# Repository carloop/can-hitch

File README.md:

# CAN Hitch
## _A CAN Bus Transceiver Breakout_

Connect microcontrollers together with CAN bus.

- [Schematics](CAN-breakout-3.3V-v3.pdf)
- [Bill of materials](CAN-breakout-3.3V-v3_BOM.csv)

## License

Copyright 2017 Carloop
Released under the MIT license

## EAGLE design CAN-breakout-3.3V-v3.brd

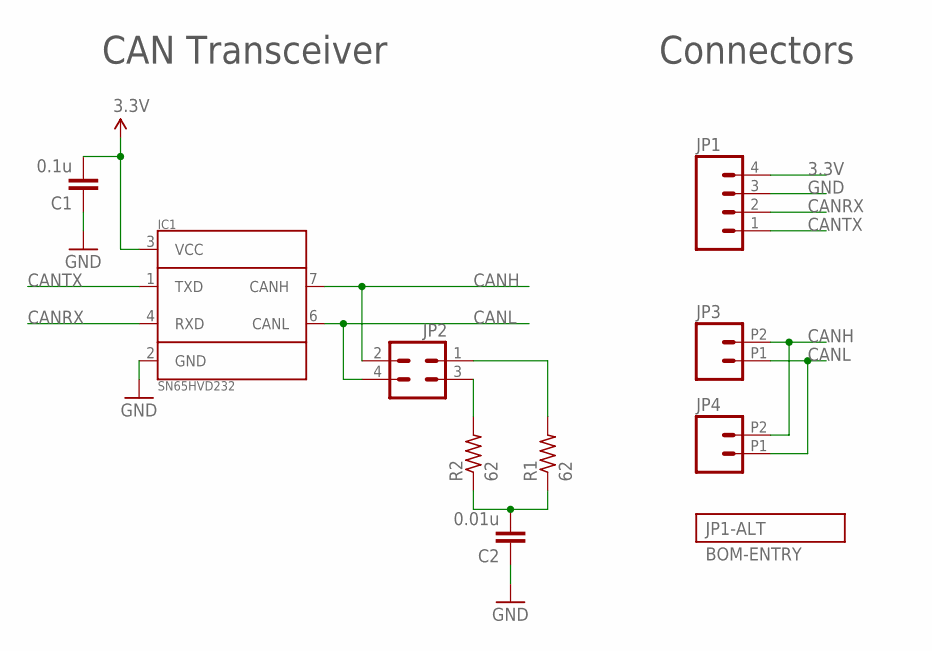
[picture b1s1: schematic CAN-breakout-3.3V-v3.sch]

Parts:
C1: 0.1u; C1206; PARTNO 12065C104KAT2A
C2: 0.01u; C1206; PARTNO 12065C103KAT2A
IC1: SN65HVD232; SO8; PARTNO SN65HVD232DR
JP1: M04PTH; 1X04; PARTNO PREC004SAAN-RC
JP2: M02X2; 2X2; PARTNO PREC002DAAN-RC
JP3, JP4: M022.54MM_SCREWTERM; 1X02_2.54_SCREWTERM; PARTNO OSTVN02A150
R1, R2: 62; R1206; PARTNO RC1206FR-0762RL

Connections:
3.3V: C1.2, IC1.3 (VCC), JP1.4
CANH: IC1.7 (CANH), JP2.2, JP3.P2 (2), JP4.P2 (2)
CANL: IC1.6 (CANL), JP2.4, JP3.P1 (1), JP4.P1 (1)
CANRX: IC1.4 (RXD), JP1.2
CANTX: IC1.1 (TXD), JP1.1
GND: C1.1, C2.1, IC1.2 (GND), JP1.3
unnamed: JP2.1, R1.2
unnamed: C2.2, R1.1, R2.1
unnamed: JP2.3, R2.2

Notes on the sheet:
CAN Transceiver
Connectors

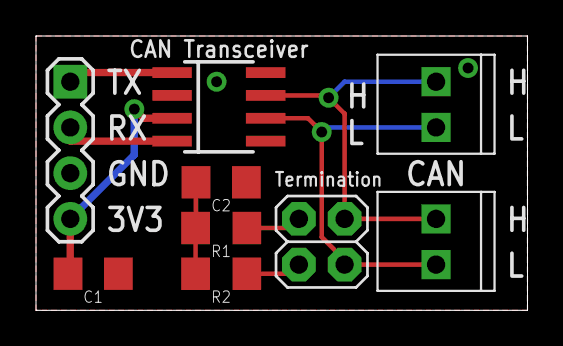
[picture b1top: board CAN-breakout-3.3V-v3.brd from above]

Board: 2 copper layers, 27.3 x 15.2 mm, 9 parts (0 on the bottom side), 9 nets.

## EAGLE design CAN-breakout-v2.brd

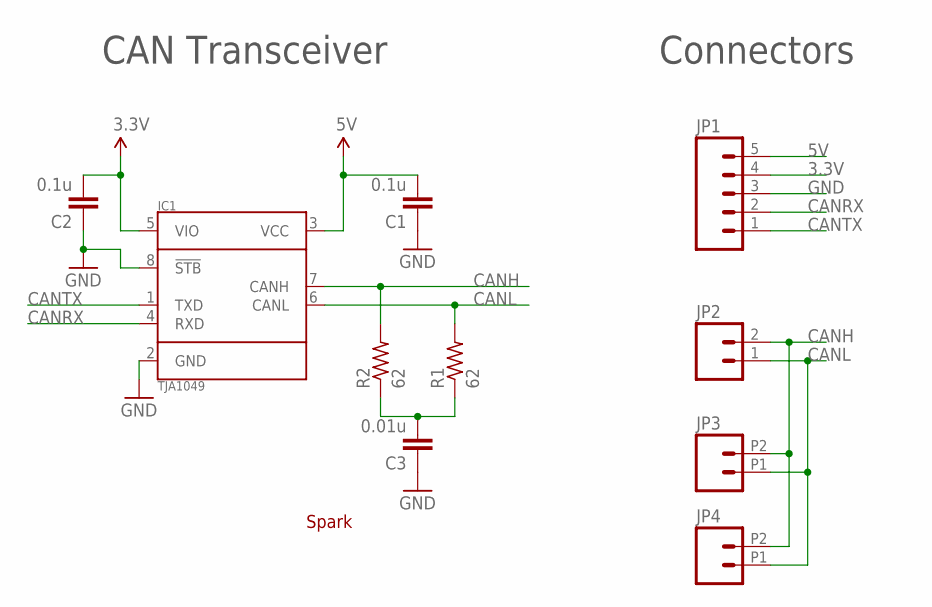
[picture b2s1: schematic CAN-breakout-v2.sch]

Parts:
C1, C2: 0.1u; C1206; PARTNO 12065C104KAT2A
C3: 0.01u; C1206; PARTNO 12065C103KAT2A
IC1: TJA1049; SO8; PARTNO TJA1049T-118
JP1: M05PTH; 1X05; PARTNO PREC005SAAN-RC
JP2: M02PTH; 1X02; PARTNO PREC002SAAN-RC
JP3, JP4: M022.54MM_SCREWTERM; 1X02_2.54_SCREWTERM; PARTNO OSTVN02A150
R1, R2: 62; R1206; PARTNO RC1206FR-0762RL
U$3: SPARK_LOGO2

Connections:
3.3V: C2.2, IC1.5 (VIO), JP1.4
5V: C1.2, IC1.3 (VCC), JP1.5
CANH: IC1.7 (CANH), JP2.2, JP3.P2 (2), JP4.P2 (2), R2.2
CANL: IC1.6 (CANL), JP2.1, JP3.P1 (1), JP4.P1 (1), R1.2
CANRX: IC1.4 (RXD), JP1.2
CANTX: IC1.1 (TXD), JP1.1
GND: C1.1, C2.1, C3.1, IC1.2 (GND), IC1.8 (!STB), JP1.3
unnamed: C3.2, R1.1, R2.1

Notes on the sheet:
CAN Transceiver
Connectors

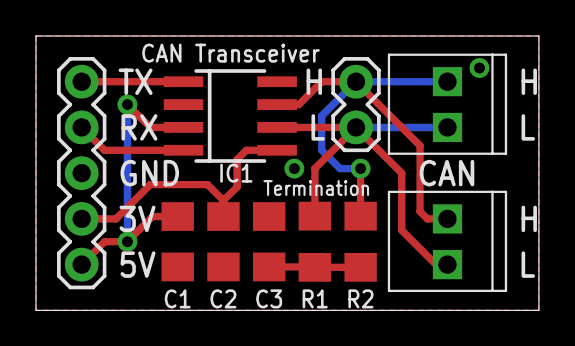
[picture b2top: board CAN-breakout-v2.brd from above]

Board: 2 copper layers, 27.9 x 15.2 mm, 11 parts (1 on the bottom side), 8 nets.

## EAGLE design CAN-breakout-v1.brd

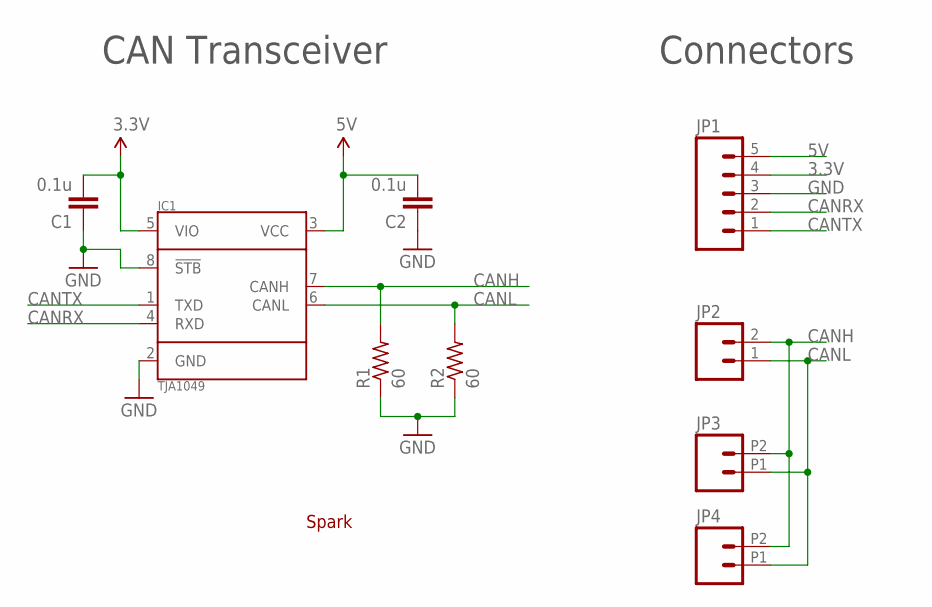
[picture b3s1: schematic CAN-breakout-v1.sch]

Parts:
C1, C2: 0.1u; C1206; PARTNO GRM155R71C104KA88D
IC1: TJA1049; SO8; PARTNO TJA1049T-118
JP1: M05PTH; 1X05; PARTNO PREC005SAAN-RC
JP2: M02PTH; 1X02; PARTNO PREC002SAAN-RC
JP3, JP4: M022.54MM_SCREWTERM; 1X02_2.54_SCREWTERM; PARTNO OSTVN02A150
R1: 60; R1206; PARTNO ERJ-2RKF6202X
R2: 60; R1206; PARTNO ERJ-2RKF1002X
U$3: SPARK_LOGO2

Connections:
3.3V: C1.2, IC1.5 (VIO), JP1.4
5V: C2.2, IC1.3 (VCC), JP1.5
CANH: IC1.7 (CANH), JP2.2, JP3.P2 (2), JP4.P2 (2), R1.2
CANL: IC1.6 (CANL), JP2.1, JP3.P1 (1), JP4.P1 (1), R2.2
CANRX: IC1.4 (RXD), JP1.2
CANTX: IC1.1 (TXD), JP1.1
GND: C1.1, C2.1, IC1.2 (GND), IC1.8 (!STB), JP1.3, R1.1, R2.1

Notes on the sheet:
CAN Transceiver
Connectors

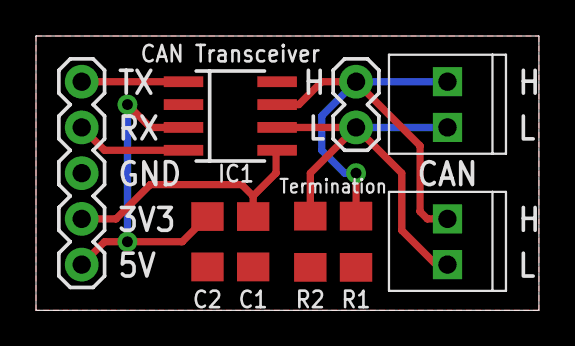
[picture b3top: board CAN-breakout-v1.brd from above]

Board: 2 copper layers, 27.9 x 15.2 mm, 10 parts (1 on the bottom side), 7 nets.

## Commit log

2017-03-17 First version sent to OSH Park
2017-03-17 Add images
2017-03-17 Fix the termination
2017-03-17 Pics v2
2017-03-17 quote csv properly
2017-03-27 Add 3.3V variant
2017-03-29 Create Gerbers
2017-03-31 Update layout files
2017-03-31 Rename project
2017-03-31 Rename
2017-04-21 Added jumper to CAN-hitch-v3_BOM.csv

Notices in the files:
parts and their libraries:
SparkFun-Connectors: Licensing: Creative Commons ShareAlike 4.0 International - https://creativecommons.org/licenses/by-sa/4.0
SparkFun-Aesthetics: Licensing: CC v3.0 Share-Alike You are welcome to use this library for commercial purposes.
bom: Copyright (C) 2010, Bob Starr
